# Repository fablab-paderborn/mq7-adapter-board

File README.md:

MQ7 Adapter Board
=================

This board implement the circuit proposed by home assistant to enable the
proper cycling of the sensor: https://devices.esphome.io/devices/MQ-7

It provides a cleaner and easier to accomplish (in some regards) solution
compared to modifying the original breakout board. You can also source
the parts without the original board.

This board does not include a power led that is lit when 5V is present
as I did not find that particular useful. 

Notes
=====

There are a few design choices for the board. Some of them them, e.g. 
the selection of R1 also apply if you do the modification on the
original breakout board.

Selection of R1
---------------
The MQ7 and MQ7B require different resistors for R1. The 75Ω used in the 
circuit here will result in 1.5V voltage across the heating element in the 
MQ7 when HEAT input is low, which is the required value for the MQ7B. If 
you are using a MQ7, the voltage should be 1.4V. This requires R1 to be 82Ω
or 86Ω assuming 33Ω for the heater itself.

It should also be possible to leave R1 unpopulated and use PWM with a duty
cycle that is equivalent to 1.4V/1.5V instead and save the 160mW that this
resistor burns but I have not tested that.

Selection of R5
---------------
When going with the original schematics, R5 is 0Ω and just be bridged
by solder.  If you want to play a bit safer and protect the IO pin of
ESP, it is recommended to use something like 100Ω here.

Order of pins
------------
Please note that VCC and GND are reversed in comparison to the common MQ7
breakout board that constantly heats the sensor.

Holes for the MQ7 sensor
------------------------
The holes for the MQ7 are 1mm. This is enough for new sensors. If you 
desoldered an MQ7 sensor, you might need to enlarge the holes a bit to
fit a desoldered sensors or adjust the hole sizes in the project.

Finished board
==============

Schematics
==========

Bill of materials
=================

| Qty | Reference | Value     | Notes                                        |
|----:|-----------|-----------|----------------------------------------------|
|   1 | C1        | 100nF     |                                              |
|   1 | J1        | Conn 1x4  |                                              |
|   1 | Q1        | IRLML2502 | Or other SOT23 N-channel mosfet, e.g. SL2310 |
|   1 | R1        | 75        | or 82Ω/86Ω. See Note on selection of R1      |
|   2 | R2,R3     | 1k        |                                              |
|   1 | R4        | 470       |                                              |
|   1 | R5        | 100       | Or 0Ω See note on R5                         | 
|   1 | U1        | MQ-7      |                                              |

The IRLML2502 transistor is the one that I had on hand and used. The original
modification recommends the SL2310. But any N-Channel mosfet with V_GS < 3.3V
that can handle the ~150 mA should work fine.

License
=======
This project is licensed under the 
[CC BY-SA 4.0](https://creativecommons.org/licenses/by-sa/4.0/) license

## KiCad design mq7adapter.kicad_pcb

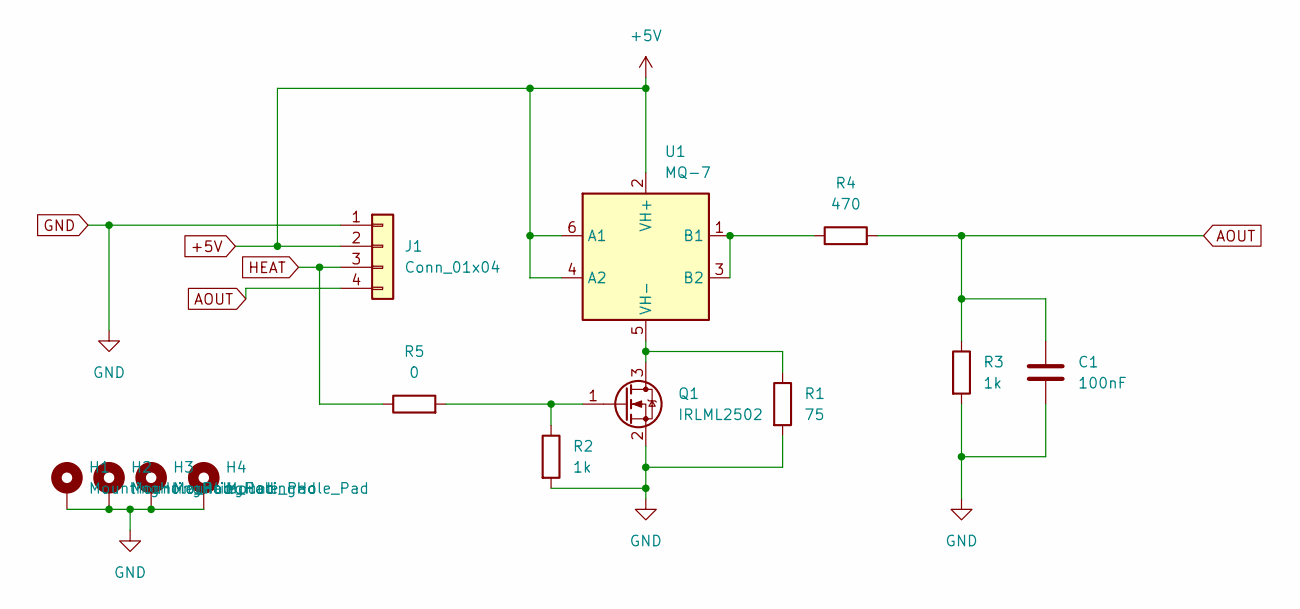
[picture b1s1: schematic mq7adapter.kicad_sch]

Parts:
C1: 100nF; C_1206_3216Metric_Pad1.33x1.80mm_HandSolder
H1, H2, H3, H4: MountingHole_Pad; MountingHole_2.5mm_Pad
J1: Conn_01x04; PinHeader_1x04_P2.54mm_Vertical
Q1: IRLML2502; SOT-23_Handsoldering
R1: 75; R_1206_3216Metric_Pad1.30x1.75mm_HandSolder
R2, R3: 1k; R_1206_3216Metric_Pad1.30x1.75mm_HandSolder
R4: 470; R_1206_3216Metric_Pad1.30x1.75mm_HandSolder
R5: 0; R_1206_3216Metric_Pad1.30x1.75mm_HandSolder
U1: MQ-7; MQ-6

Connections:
+5V: J1.2, U1.2 (VH+), U1.4 (A2), U1.6 (A1)
AOUT: C1.1, J1.4, R3.1, R4.2
GND: C1.2, H1.1, H2.1, H3.1, H4.1, J1.1, Q1.2 (S), R1.2, R2.2, R3.2
HEAT: J1.3, R5.1
unnamed: Q1.3 (D), R1.1, U1.5 (VH-)
unnamed: Q1.1 (G), R2.1, R5.2
unnamed: R4.1, U1.1 (B1), U1.3 (B2)

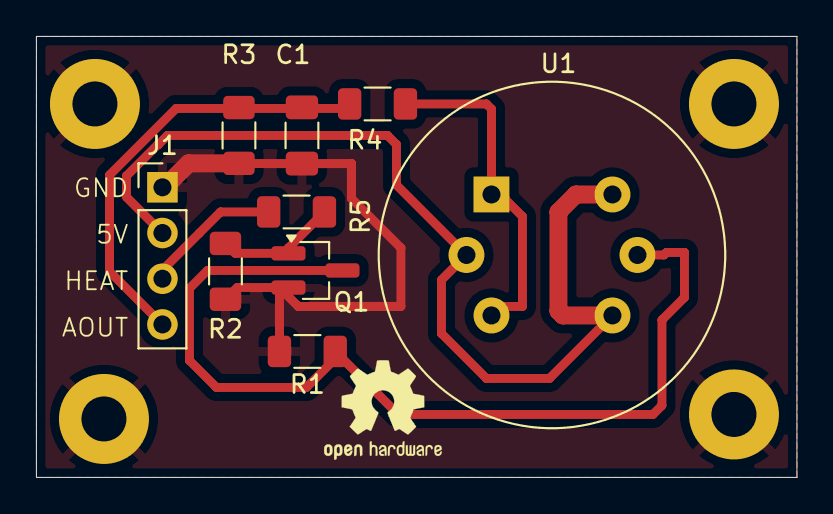
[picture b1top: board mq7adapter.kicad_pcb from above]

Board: 2 copper layers, 42.2 x 24.5 mm, 13 parts (0 on the bottom side), 7 nets.
